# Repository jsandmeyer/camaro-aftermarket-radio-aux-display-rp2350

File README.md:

## Camaro Temperature & Reverse Sensor Display Shim - RP2350

### Differences from [other repository](https://github.com/jsandmeyer/camaro-aftermarket-radio-aux-display)

This version uses an RP2350 (Raspberry Pi Pico 2 IC) instead of an ATMEGA328PB (Arduino Uno mod).

It takes advantage of the two cores so it can:
1. Listen to the CANBus while rendering is happening, without interrupting either
2. Listen to the CANBus without a CAN controller

### Summary

This provides resources to help you build something to get the temperature display of a PAC RPK5-GM4102 (or 4101) to function while using a Maestro RR instead of the box that came with the PAC kit.
This is useful if you want to have the Maestro functions to get/update vehicle data, but have the nice function and appearance of the OEM-style HVAC knobs provided by the PAC kit.

### Important
This project is not endorsed by GM, the makers of any trim kits (PAC, iDatalink, etc) or my aftermarket radio, any forum or their users, or anyone else, including any entities named in this repository.
It is a personal project that I have completed, and I have accepted a risk to my own property by building and installing this project.

This project (except for PCB footprints supplied by KiCad's included files) is licensed under the MIT license.
Please read the attached LICENSE document.
All code was written by myself, based on documentation provided by libraries or electronic part providers.
All PCB design (except for some footprints) was completed by myself.

### Background

[This forum post on camaro5.com](https://www.camaro5.com/forums/showthread.php?t=588249) goes over the process of combining the two dash kit elements.
Note the OP and others never got the temperature display to work.
This is because the PAC trim component's harness does not have CANBUS access, and the PAC controller was relaying the temperature (and possibly other data) over the Serial line running between the radio and HVAC harnesses.

### Goal

My goal was simply to display the temperature on the OLED.
In the process of design, I also decied to have it show backup sensor data.
The original MyLink radio showed a triangle with an exclamation point in one of five positions over the backup camera when reversing, and it would change color and flash depending on distance.
I wanted to display something similar on the OLED when reversing, because no aftermarket radios seem to support showing the backup sensor data AND camera view at the same time!
The latest version of this module is also able to determine whether the car is displaying metric or imperial units, so there is no need to adjust the jumper on the PCB.

### Reverse Engineering the Hardware

I was able to do some reverse engineering of the PAC RPK5, but without a logic analyzer or serial reading device, I could not do so completely.
I did determine that if I depinned the PAC harness to include only power input, net 5060 low-speed GMLAN, and net 7458 serial data, it would power on and the temperature would display.
However, if I disconnected the TX pin on the PAC controller's internal CANBUS modem (as suggested by its documentation, would force it into "read-only" mode) it would fail completely.
I also discovered that the OLED board used by PAC is a very standard SSD1306 SPI model, and it's roughly equivalent to something you could buy off a hobby site - and the cable connector is also a standard Molex PicoBlade (though the included cable is a crossover cable, likely not made by Molex).

### Reverse Engineering the CANBUS

#### Hardware and Software

I used an Arduino Uno and the [Sparkfun CANBUS shield](https://www.sparkfun.com/products/13262) to prove viability.
With this setup, I was able to snoop on my car's low-speed CANBUS (net 5060) via the main ODB connector using pin 1 for CAN_H and pin 4 for CAN_L and GND.
Using the [mcp_can library](https://github.com/coryjfowler/MCP_CAN_lib) I was able to read temperature and other data.
Eventually, some light googling got me [some details](https://docs.google.com/spreadsheets/d/1pFdixF6W0XK4SR6pXHIlZaFRo9qM5XmAWOK7JcAQdDM/) regarding CANBUS IDs for this car and for other GM cars.

My configuration for this was to:
* Call `CAN0.begin(MCP_STDEXT, CAN_33K3BPS, MCPHZ)` to initialize low-speed CANBUS at 33.3k.
* To configure the filters, I used online resources to try to determine what different ARB IDs meant, and in some cases, even turned off filtering and simply looked through the stream for messages.
* Call `CAN0.setMode(MCP_LISTENONLY)` for read-only CANBUS operation

#### Hardware V2

After confirming this configuration, I switched to using a bare ATMEGA328P chip (similar to the VQFN package I would use in production) and a MCP25625 CAN controller with transciever.
I added ferrite beads to the OLED connector after seeing that PAC decided to use them in their controller board.
I also added a switch to allow selection of Metric vs Imperial units.

#### Hardware V3

This is the first production version.
I added a nice TI power supply designed via Webench, soldered everything down, and also used a jumper to select Metric vs Imperail units (in place of the switch).
Some SMT components are slightly different, like using an AMEGA328PB instead of the ATMEGA328P, or the different footprint of the oscillator.

#### Hardware V6

Versions 4 and 5 had issues which prevented them from going to production.
This version includes mounting holes, extra power supply filtering, a watchdog to reboot the MCU if there are too many errors during boot, and auto-sensing of temperature/distance units instead of using a jumper.
The circuit also uses the 3.3V power supply for all logic except for the CAN transciever, which runs on the base 5V.

#### Hardware V7

This uses an RP2350 MCU instead of an ATMEGA328PB.
See the notes above.

It also uses a TCAN332 transciever instead of the MCP25625 (MCP2551-style).
The IC is effectively a drop-in replacement for the MCP-2551 (except that no slope control resistor is needed).
The main benefit is that it runs on 3.3V, so only one power suppy is necessary (in addition to the 1.1V inside the RP2350).

#### Logs

Temperature was easy to figure out, and was my first step.

For my 2014 Camaro, it comes in as 0x10424060 (raw header), or 0x212 (with mask).
The second byte `buf[1]` contains the temperature... kind-of.
You have to divide the hex value by two, and subtract 40, to get degrees in celsius.

The backup sensors took more work to understand, but were still straightforward.

I found that they were streaming data on 0x103A80BB (raw header), or 0x1D4 (with mask).

The *second nibble* of the first byte `buf[0] & 0x0F` indicates the park-assist staus.
A value of `0` indicates park-assist is ON, and a value of `F` indicates it is OFF.
The *first nibble* `buf[0] & 0xF0` seems related to something else, and also seemed to vary.

The Bosch parking assist unit seems to report the direction and distance to the *closest* object only.
The second byte `buf[1]` contains the distance, in cm, from 0-255cm.

The position is more complicated.
The Bosch unit has four sensors, but reports three positional channels: Middle, Right, and Left.
It may report a single positional channel, or two adjacent channels, to form five possible locations to render the warning triangle!
The position comes out in bytes 3-4 `buf[2-3]`, split into nibbles indicating positions `[M, R], [N/A, L]`.
A value of 0 indicates the channel is off, but values of 1 thorugh 5 indicate the relative "closeness" and beep/flash speed, with 1 being closest and 5 being furthest.
If two channels are activated, such as to indicate a middle-left obstruction, both channels would have the same value.
I also decided it would be prudent to have a timeout to turn off park-assist display if no data was received, in case the MCU missed the "off" signal.

Lastly, I decided to use data from ARB ID 0x425 to decide whether to use Imperial or Metric units.
The vehicle sends this data multiple times upon startup, so devices using only ACC power (like this) can receive it.

### Assembly

**WARNING: DO THIS ALL AT YOUR OWN RISK.  YOU MAY DAMAGE YOUR CAR OR OTHER EQUIPMENT.  MY DESIGNS PROBABLY HAVE FLAWS; I AM A WEB SOFTWARE ENGINEER AFTER ALL.**

The minimum for this to work is that you need the entire PAC kit, a Maestro RR and its standard cables, and a harness to connect the Maestro RR to the camaro.
For the main harness, you can use the one that comes with the complete iDatalink kit, or just the HRN-HRR-GM2 if you want to re-pin the harness (mandatory).

If you use the harness with the iDatalink trim kit, just leave the HVAC connector and trim connector hanging.
For the cheap option, I originally removed pins 2, 13, 20, and 23 from the HRN-HRR-GM2 to make it seem to work.
If you are particularly clever, you might be able to figure out how to wire in the car's microphone to the harness, like the PAC kit does, and connect it to a 3.5mm jack for the radio.
However, for my final build, I did use the harness included in the KIT-CAM1 with the HVAC control disconnected.

I spliced into the 5060 Low-Speed GMLAN cable, the GND line, and the red "accessory power" line between the Maestro RR unit and my aftermarket radio to power the circuit board.

I used a non-crossover Molex Picoblade cable (pre-assembled, Molex part number 0151340703) to connect the circuit board to the OLED display.
I had to temporarily remove a retaining clip from the RPK5 trim to install the cable.
The cable included in the RPK5 is a crossover cable, **please do not use the included display cable for this project** since all the pins will be backwards.
The connector on this project was designed to match the use of a longer cable from Molex; and was *not* based on the design in the trim kit.

See my analysis of the various harness connector configurations in the `resources/2014 camaro connectors.xlsx` file in this repository.

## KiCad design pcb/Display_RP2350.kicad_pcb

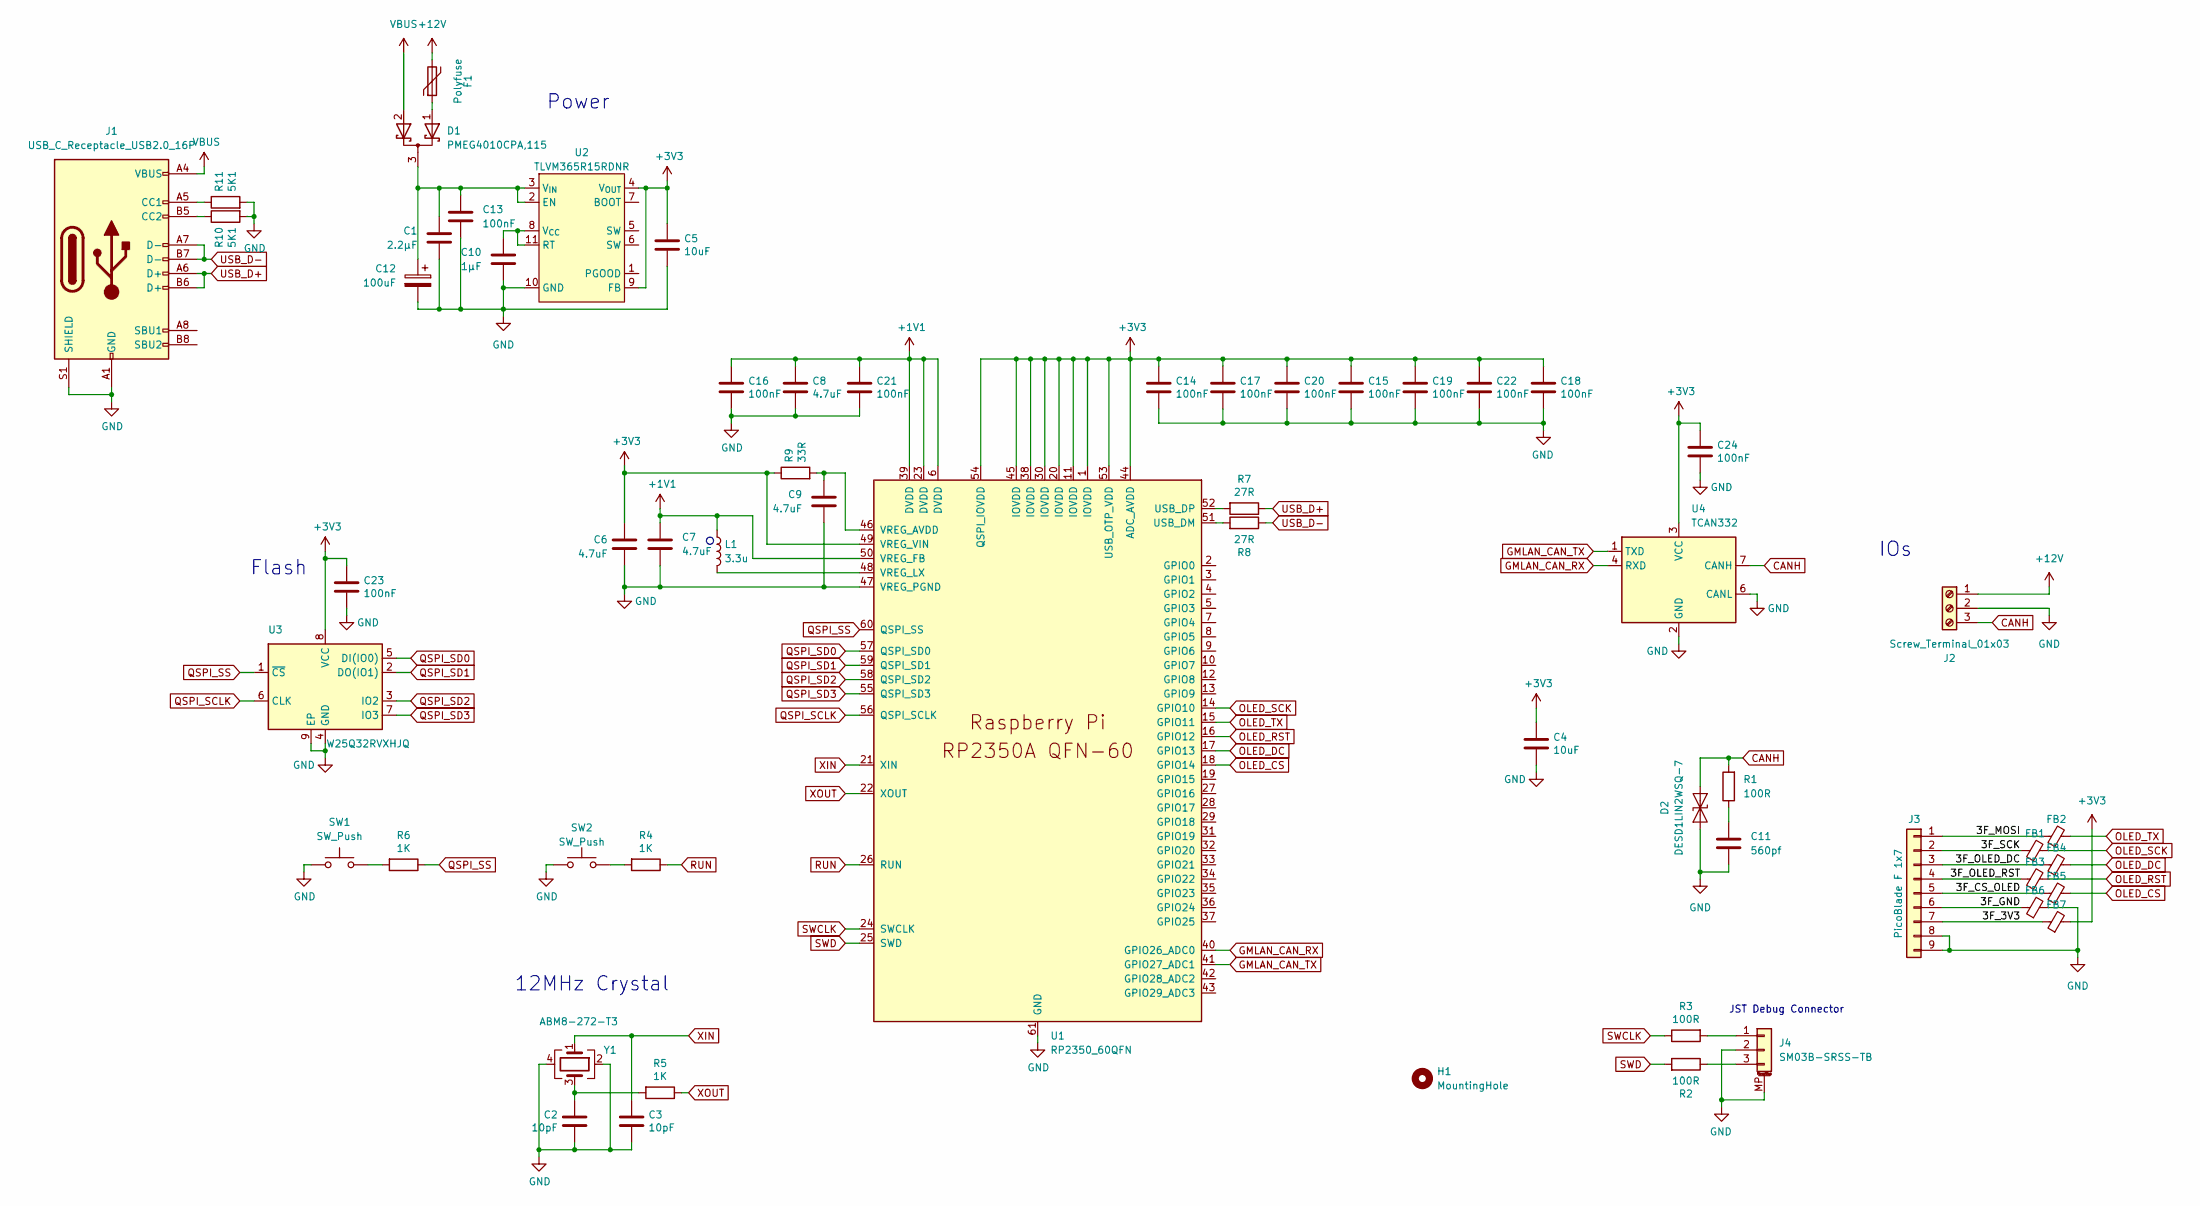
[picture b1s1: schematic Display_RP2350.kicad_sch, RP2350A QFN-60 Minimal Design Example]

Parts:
C1: 2.2µF; C_1206_3216Metric
C2, C3: 10pF; C_0402_1005Metric
C4, C5: 10uF; C_0805_2012Metric
C6, C7: 4.7uF; C_0402_1005Metric_small_pads
C8, C9: 4.7uF; C_0402_1005Metric
C10: 1µF; C_0603_1608Metric
C11: 560pf; C_0402_1005Metric
C12: 100uF; CP_Elec_6.3x7.7
C13, C14, C15, C16, C17, C18, C19, C20, C21, C22, C23, C24: 100nF; C_0402_1005Metric
D1: PMEG4010CPA,115; HUSON-3-1EP_2x2mm_P1.3mm_EP1.1x1.6mm
D2: DESD1LIN2WSQ-7; D_SOD-323
F1: Polyfuse; Fuse_1206_3216Metric
FB1, FB2, FB3, FB4, FB5, FB6, FB7: 120X; L_0402_1005Metric
H1: MountingHole; MountingHole_2.2mm_M2_ISO14580
J1: USB_C_Receptacle_USB2.0_16P; USB_C_Receptacle_GCT_USB4105-xx-A_16P_TopMnt_Horizontal
J2: Screw_Terminal_01x03; TerminalBlock_3P
J3: PicoBlade F 1x7; CON_532610771_MOD
J4: SM03B-SRSS-TB; JST_SH_SM03B-SRSS-TB_1x03-1MP_P1.00mm_Horizontal
L1: 3.3u; L_pol_2016
R1, R2, R3: 100R; R_0402_1005Metric
R4, R5, R6: 1K; R_0402_1005Metric
R7, R8: 27R; R_0402_1005Metric
R9: 33R; R_0402_1005Metric
R10, R11: 5K1; R_0402_1005Metric
SW1, SW2: SW_Push; SW_Push_1P1T_NO_Vertical_Wuerth_434133025816
U1: RP2350_60QFN; QFN-60-1EP_7x7mm_P0.4mm_EP3.4x3.4mm
U2: TLVM365R15RDNR; QFN-FCMOD_TI_11B
U3: W25Q32RVXHJQ; Winbond_USON-8-1EP_3x2mm_P0.5mm_EP0.2x1.6mm
U4: TCAN332; TSOT-23-8
Y1: ABM8-272-T3; Crystal_SMD_3225-4Pin_3.2x2.5mm

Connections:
+1V1: C7.1, C8.1, C16.1, C21.1, L1.1, U1.6 (DVDD), U1.23 (DVDD), U1.39 (DVDD), U1.50 (VREG_FB)
+3V3: C4.1, C5.1, C6.1, C14.1, C15.1, C17.1, C18.1, C19.1, C20.1, C22.1, C23.1, C24.1, FB7.2, R9.1, U1.1 (IOVDD), U1.11 (IOVDD), U1.20 (IOVDD), U1.30 (IOVDD), U1.38 (IOVDD), U1.44 (ADC_AVDD), U1.45 (IOVDD), U1.49 (VREG_VIN), U1.53 (USB_OTP_VDD), U1.54 (QSPI_IOVDD), U2.4 (V_{OUT}), U2.9 (FB), U3.8 (VCC), U4.3 (VCC)
+12V: F1.2, J2.1
/3F_3V3: FB7.1, J3.7
/3F_CS_OLED: FB5.1, J3.5
/3F_GND: FB6.1, J3.6
/3F_MOSI: FB2.1, J3.1
/3F_OLED_DC: FB4.1, J3.3
/3F_OLED_RST: FB3.1, J3.4
/3F_SCK: FB1.1, J3.2
CANH: D2.2 (A2), J2.3, R1.2, U4.7 (CANH)
GMLAN_CAN_RX: U1.40 (GPIO26_ADC0), U4.4 (RXD)
GMLAN_CAN_TX: U1.41 (GPIO27_ADC1), U4.1 (TXD)
GND: C1.2, C2.2, C3.2, C4.2, C5.2, C6.2, C7.2, C8.2, C9.2, C10.2, C11.2, C12.2, C13.2, C14.2, C15.2, C16.2, C17.2, C18.2, C19.2, C20.2, C21.2, C22.2, C23.2, C24.2, D2.1 (A1), FB6.2, J1.A1 (GND), J1.A12 (GND), J1.B1 (GND), J1.B12 (GND), J1.S1 (SHIELD), J2.2, J3.8, J3.9, J4.2, J4.MP (MountPin), R10.2, R11.2, SW1.1, SW2.2, U1.47 (VREG_PGND), U1.61 (GND), U2.10 (GND), U3.4 (GND), U3.9 (EP), U4.2 (GND), U4.6 (CANL), Y1.2, Y1.4
unnamed: C2.1, R5.2, Y1.3
unnamed: C11.1, R1.1
unnamed: D1.1 (A), F1.1
unnamed: C1.1, C12.1, C13.1, D1.3 (K), U2.2 (EN), U2.3 (V_{IN})
unnamed: J1.A5 (CC1), R11.1
unnamed: J1.B5 (CC2), R10.1
unnamed: J4.1, R3.2
unnamed: J4.3, R2.1
unnamed: R4.2, SW2.1
unnamed: R6.2, SW1.2
unnamed: R8.2, U1.51 (USB_DM)
unnamed: R7.2, U1.52 (USB_DP)
unnamed: C9.1, R9.2, U1.46 (VREG_AVDD)
unnamed: L1.2, U1.48 (VREG_LX)
unnamed: C10.1, U2.8 (V_{CC}), U2.11 (RT)
OLED_CS: FB5.2, U1.18 (GPIO14)
OLED_DC: FB4.2, U1.17 (GPIO13)
OLED_RST: FB3.2, U1.16 (GPIO12)
OLED_SCK: FB1.2, U1.14 (GPIO10)
OLED_TX: FB2.2, U1.15 (GPIO11)
QSPI_SCLK: U1.56 (QSPI_SCLK), U3.6 (CLK)
QSPI_SD0: U1.57 (QSPI_SD0), U3.5 (DI(IO0))
QSPI_SD1: U1.59 (QSPI_SD1), U3.2 (DO(IO1))
QSPI_SD2: U1.58 (QSPI_SD2), U3.3 (IO2)
QSPI_SD3: U1.55 (QSPI_SD3), U3.7 (IO3)
QSPI_SS: R6.1, U1.60 (QSPI_SS), U3.1 (~CS)
RUN: R4.1, U1.26 (RUN)
SWCLK: R3.1, U1.24 (SWCLK)
SWD: R2.2, U1.25 (SWD)
USB_D+: J1.A6 (D+), J1.B6 (D+), R7.1
USB_D-: J1.A7 (D-), J1.B7 (D-), R8.1
VBUS: D1.2 (A), J1.A4 (VBUS), J1.A9 (VBUS), J1.B4 (VBUS), J1.B9 (VBUS)
XIN: C3.1, U1.21 (XIN), Y1.1
XOUT: R5.1, U1.22 (XOUT)

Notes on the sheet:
JST Debug Connector
IOs
Flash
12MHz Crystal
Power

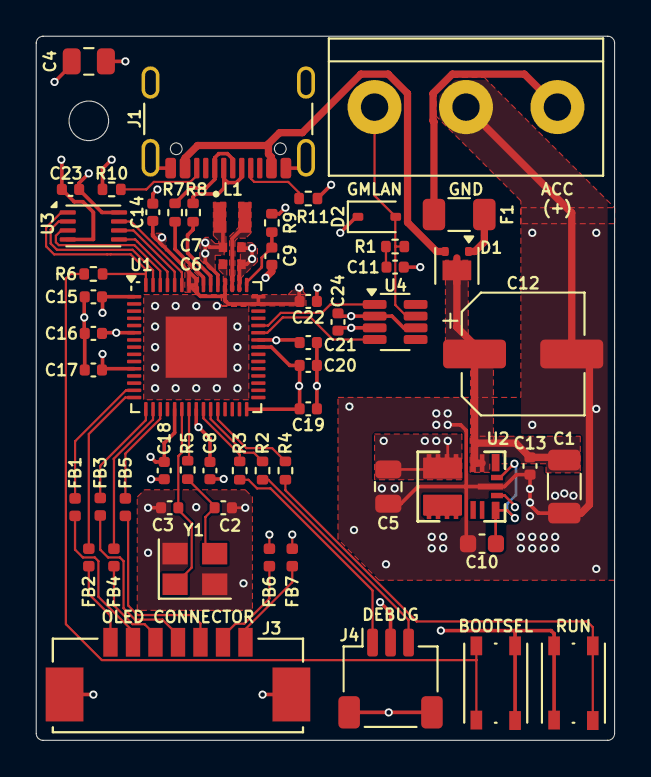
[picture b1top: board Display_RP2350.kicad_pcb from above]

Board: 4 copper layers, 32.1 x 39.1 mm, 58 parts (0 on the bottom side), 48 nets.

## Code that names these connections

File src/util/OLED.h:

#ifndef CAMARO_DISPLAY_OLED_H
#define CAMARO_DISPLAY_OLED_H

// OLED display measurements
#define SCREEN_WIDTH 128
#define SCREEN_HEIGHT 32

#define OLED_SPI_BAUD 1000000UL

#define OLED_RX 8 // 11
#define OLED_CS 9 // 12
#define OLED_SCK 10 // 14
#define OLED_TX 11 // 15

#define OLED_RST 12 // 16
#define OLED_DC 13 // 17
#define SPI_CS_PIN_OLED 14 // 19

#endif //CAMARO_DISPLAY_OLED_H

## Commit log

2025-03-22 work on canhelper
2025-03-22 work on canhelper and renderer
2025-03-22 work on renderer
2025-03-22 fix build warnings
2025-03-22 work on renderers
2025-03-22 work on multicore
2025-03-22 remove old stuff
2025-03-22 cleanup
2025-03-23 Fix canbus startup
2025-03-23 Fix issue in backup sensor
2025-03-23 kinda get flash working
2025-03-23 clean up flash code
2025-03-23 clean up
2025-03-24 clean up multicore
2025-03-24 multicore switch from semaphore to builtin fifo since it's pre-initialized
2025-03-24 organize files
2025-03-24 clean up includes
2025-03-24 add readme
2025-03-24 clean up deps
2025-05-04 Add PCB for RP2350
2025-05-04 PCB updates
2025-05-25 Fix incorrect temperature casting
2025-05-25 Update readme & add picture
2025-06-01 env cleanup
